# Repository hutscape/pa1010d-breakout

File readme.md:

# PA1010D GPS Module Breakout board

> The PA1010D module from CDTop is the world’s smallest GNSS module with an integrated antenna, measuring only 10x10x6.8 mm. This repository contains the schematic and layout for a breadboard-able breakout board!

## Getting Started

Download the KiCad file to edit the schematic and layout: `pa1010d-breakout.pro`.

## Schematic

## Layout

Front

Back

## References

1. [CDTop PA1010D](https://www.cdtop-tech.com/products/pa1010d)
1. [PA1010D Datasheet V0.3](https://drive.google.com/file/d/1O-9RGAwgs2fgtnzJRBa9eB1fAqJt7n_k/view)
1. [Adafruit Mini GPS PA1010D](https://www.adafruit.com/product/4415)
1. [Mediatek MT3333](https://labs.mediatek.com/en/chipset/MT3333)

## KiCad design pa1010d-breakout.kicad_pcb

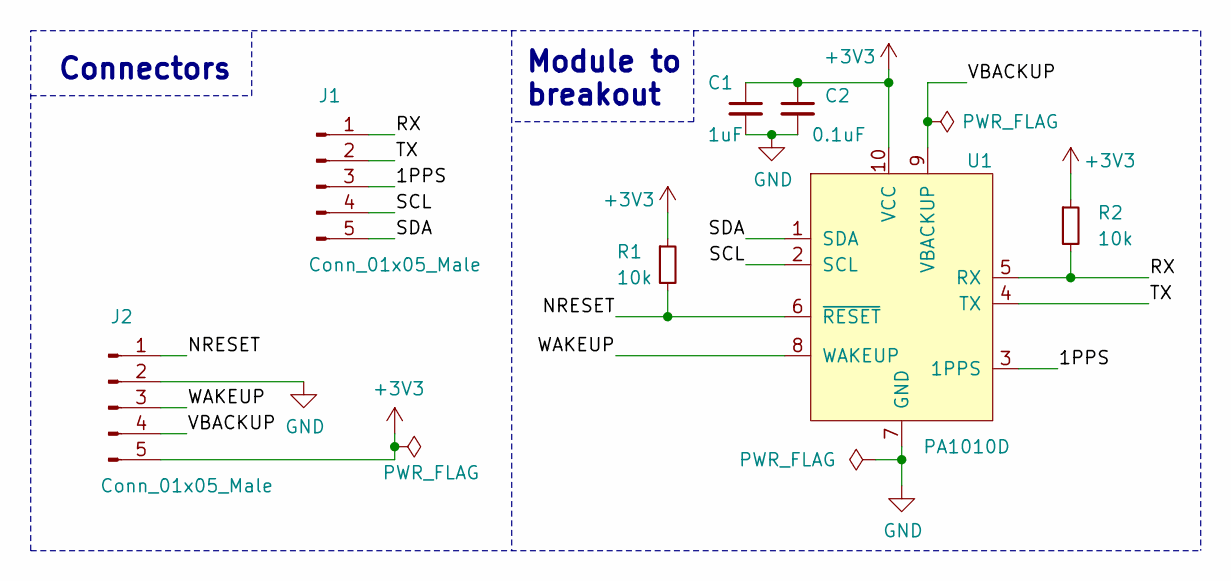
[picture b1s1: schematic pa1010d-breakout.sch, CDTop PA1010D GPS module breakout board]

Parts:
C1: 1uF; C_0805_2012Metric_Pad1.15x1.40mm_HandSolder
C2: 0.1uF; C_0805_2012Metric_Pad1.15x1.40mm_HandSolder
J1, J2: Conn_01x05_Male; PinHeader_1x05_P2.54mm_Vertical
R1, R2: 10k; R_0805_2012Metric_Pad1.15x1.40mm_HandSolder
U1: PA1010D; CDTop_MT3333_PA1010D

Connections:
+3V3: C1.1, C2.1, J2.5, R1.1, R2.1, U1.10 (VCC)
/1PPS: J1.3, U1.3 (1PPS)
/NRESET: J2.1, R1.2, U1.6 (~RESET)
/RX: J1.1, R2.2, U1.5 (RX)
/SCL: J1.4, U1.2 (SCL)
/SDA: J1.5, U1.1 (SDA)
/TX: J1.2, U1.4 (TX)
/VBACKUP: J2.4, U1.9 (VBACKUP)
/WAKEUP: J2.3, U1.8 (WAKEUP)
GND: C1.2, C2.2, J2.2, U1.7 (GND)

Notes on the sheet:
Connectors
Module to breakout

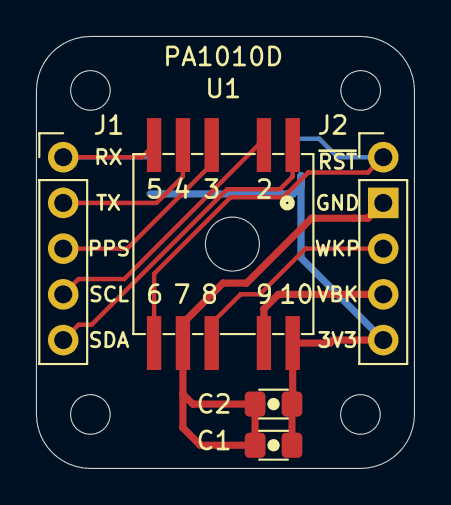
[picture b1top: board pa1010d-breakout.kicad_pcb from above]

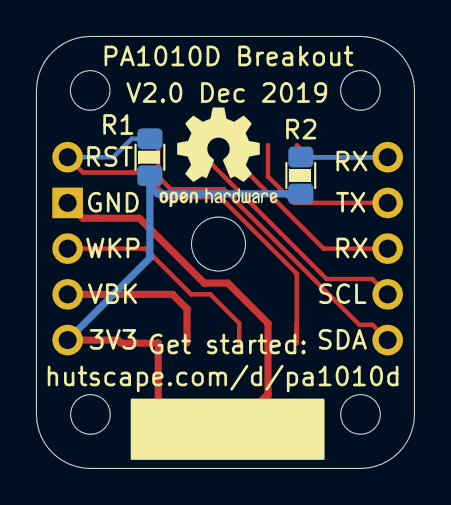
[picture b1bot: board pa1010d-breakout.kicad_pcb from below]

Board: 2 copper layers, 21.0 x 24.0 mm, 7 parts (2 on the bottom side), 10 nets.

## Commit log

2019-11-19 feat: add schematic and layout for PA10101D breakout board
2019-11-20 refactor: update PCB layout to make it smaller and add more infor in silkscreen
2019-11-29 chore: update library with panelisation footprints
2019-12-02 refactor: change to 1mm grid for edge cuts
2019-12-02 refactor: copy edge cuts layer on drawings layer as well
2019-12-02 refactor: adjust silkscreen
2019-12-02 refactor: hide reference designator J1 for header pins
2019-12-02 feat: add panelization
2019-12-14 chore: add the panelized project file
2019-12-18 docs: add version for the datasheet
2019-12-18 docs: add datasheets directory to gitignore
2019-12-18 refactor: update schematic according to datasheet V0.3
2019-12-18 refactor: elongate, rotate pads for PA1010D datasheet V0.3
2019-12-19 refactor: centralise getting started URL
2019-12-23 refactor: change pin layout for easier trace routing. close #4
2019-12-25 refactor: add pull up / down resistors
2019-12-25 refactor: change GND pad from circular to rectangular
